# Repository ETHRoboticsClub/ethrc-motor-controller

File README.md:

<h1 align="center">ETHRC Motor Controller</h1>

<p align="center" width="100%">
  
</p>

***

<p align="center">
  
&nbsp; &nbsp; &nbsp; &nbsp;
  
</p>

***

## SPECIFICATIONS

| Parameter | ETHRC Motor Controller v1.0| 
| --- | --- |
| Voltage Input | 33 - 58.8V |
| Peak Electrical Power | TBD |
| Mass | TBD |
| Peak Phase Current | TBD |
| Communication | EtherCat, 5Mbps CAN-FD and SWD interface |
| Cooling | TBD|
| Positioning | 1x Onboard 14-bit Encoder and one external encoder |
| Control rate | TBD |
| PWM Switching Rate | TBD |
| MCU | STM32G474 |
| Dimensions | 88.0 × 88.0 mm |

***

## DIRECTORY STRUCTURE

    .
    ├─ Computations       # Misc calculations
    ├─ DXF_SVG            # Vector graphics
    ├─ HTML               # HTML files for generated webpage
    ├─ Images             # Pictures and renders
    │
    ├─ kibot_resources    # External resources for KiBot
    │  ├─ colors          # Color theme for KiCad
    │  ├─ fonts           # Fonts used in the project
    │  ├─ scripts         # External scripts used with KiBot
    │  └─ templates       # Templates for KiBot generated reports
    │
    ├─ kibot_yaml         # KiBot YAML config files
    ├─ KiRI               # KiRI (PCB diff viewer) files
    │
    ├─ lib                # KiCad footprint and symbol libraries
    │  ├─ 3d_models       # Component 3D models
    │  ├─ lib_fp          # Footprint libraries
    │  └─ lib_sym         # Symbol libraries
    │
    ├─ Logos              # Logos
    │
    ├─ Manufacturing      # Assembly and fabrication documents
    │  ├─ Assembly        # Assembly documents (BoM, pos, notes)
    │  │
    │  └─ Fabrication     # Fabrication documents (ZIP, notes)
    │     ├─ Drill Tables # CSV drill tables
    │     └─ Gerbers      # Gerbers
    │
    ├─ Report             # Reports for ERC/DRC
    ├─ Schematic          # PDF of schematic
    ├─ Templates          # Title block templates
    ├─ Testing
    │  └─ Testpoints      # Testpoints tables      
    │
    └─ Variants           # Outputs for assembly variants

***

## FIRMWARE

***

## CREDITS

Schematic is largely inspired by the moteus controllers designed by Josh Pieper and amulet motion controller designed by Vincent Nguyen. They were modified to meet our own specifications. The CI/CD workflow and the templates for this KiCad 9.0 project was forked from https://github.com/nguyen-v/KDT_Hierarchical_KiBot created by Vincent Nguyen.
***

## PHOTOS

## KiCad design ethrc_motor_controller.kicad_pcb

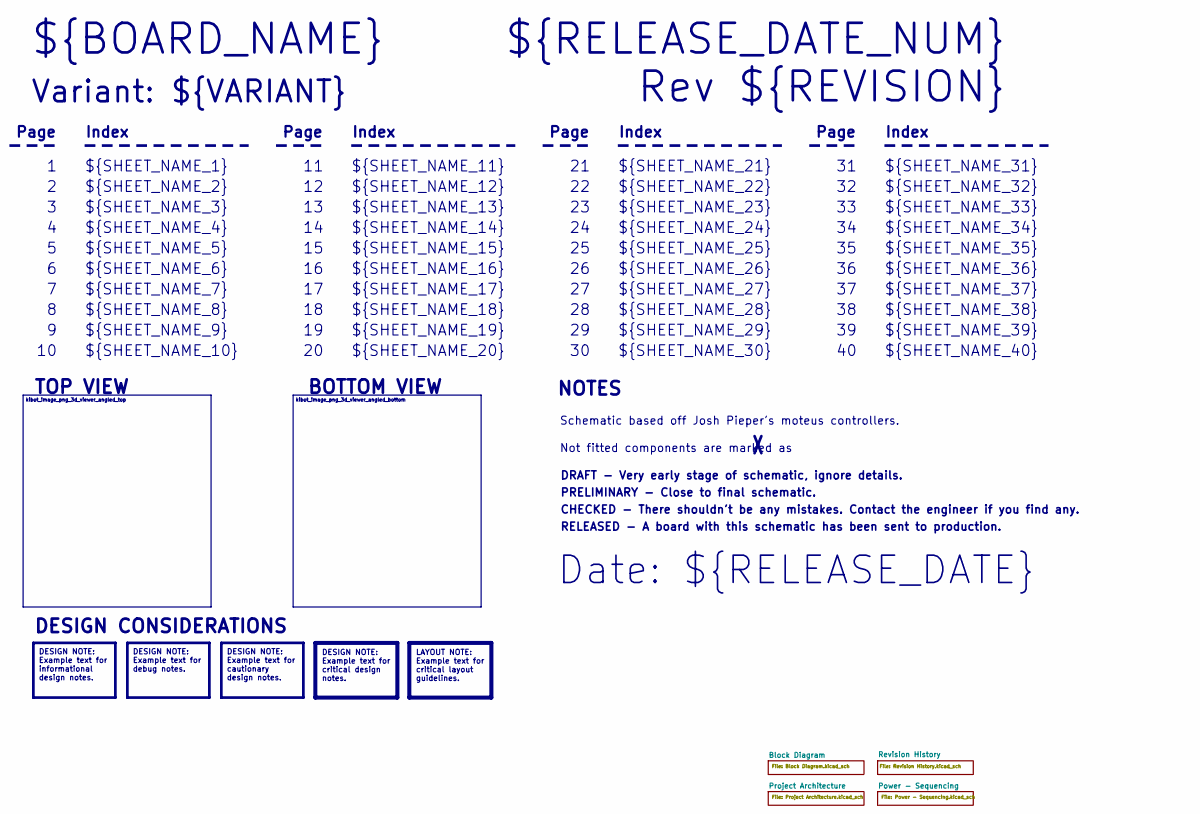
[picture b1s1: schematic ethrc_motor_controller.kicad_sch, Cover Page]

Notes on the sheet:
BOTTOM VIEW
${SHEET_NAME_23}
${SHEET_NAME_10}
RELEASED - A board with this schematic has been sent to production.
${SHEET_NAME_13}
Page
TOP VIEW
${SHEET_NAME_15}
${SHEET_NAME_7}
Not fitted components are marked as
${SHEET_NAME_30}
Index
${SHEET_NAME_18}
PRELIMINARY - Close to final schematic.
Date: ${RELEASE_DATE}
${SHEET_NAME_4}
${SHEET_NAME_27}
${SHEET_NAME_20}
${SHEET_NAME_38}
${SHEET_NAME_9}
${SHEET_NAME_12}
${SHEET_NAME_40}
${SHEET_NAME_19}
${SHEET_NAME_32}
${RELEASE_DATE_NUM}
Variant: ${VARIANT}
${SHEET_NAME_11}
${SHEET_NAME_8}
Rev ${REVISION}
${SHEET_NAME_24}
${SHEET_NAME_29}
${SHEET_NAME_22}
${SHEET_NAME_39}
${SHEET_NAME_5}
${SHEET_NAME_17}
${SHEET_NAME_28}
${SHEET_NAME_31}
${BOARD_NAME}
${SHEET_NAME_26}
${SHEET_NAME_34}

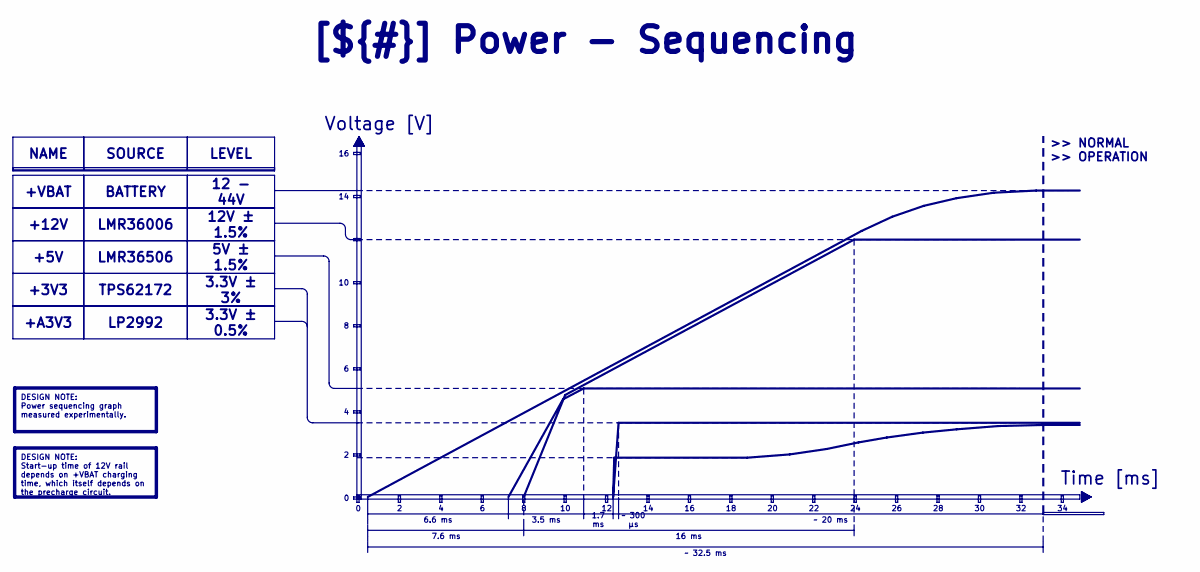
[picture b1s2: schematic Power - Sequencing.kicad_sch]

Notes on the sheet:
Voltage [V]
>> NORMAL >> OPERATION
Time [ms]
3.5 ms
7.6 ms
3.3V ± 0.5%
~ 300 μs
1.7 ms
16 ms
+12V
LP2992
LMR36006
LEVEL
NAME
DESIGN NOTE: Power sequencing graph measured experimentally.
+3V3
~ 20 ms
SOURCE
+5V
DESIGN NOTE: Start-up time of 12V rail depends on +VBAT charging time, which itself depends on the precharge circuit.
[${#}] ${TITLE}
TPS62172
LMR36506
BATTERY
5V ± 1.5%
3.3V ± 3%
+A3V3
+VBAT
6.6 ms
~ 32.5 ms
12V ± 1.5%
12 - 44V

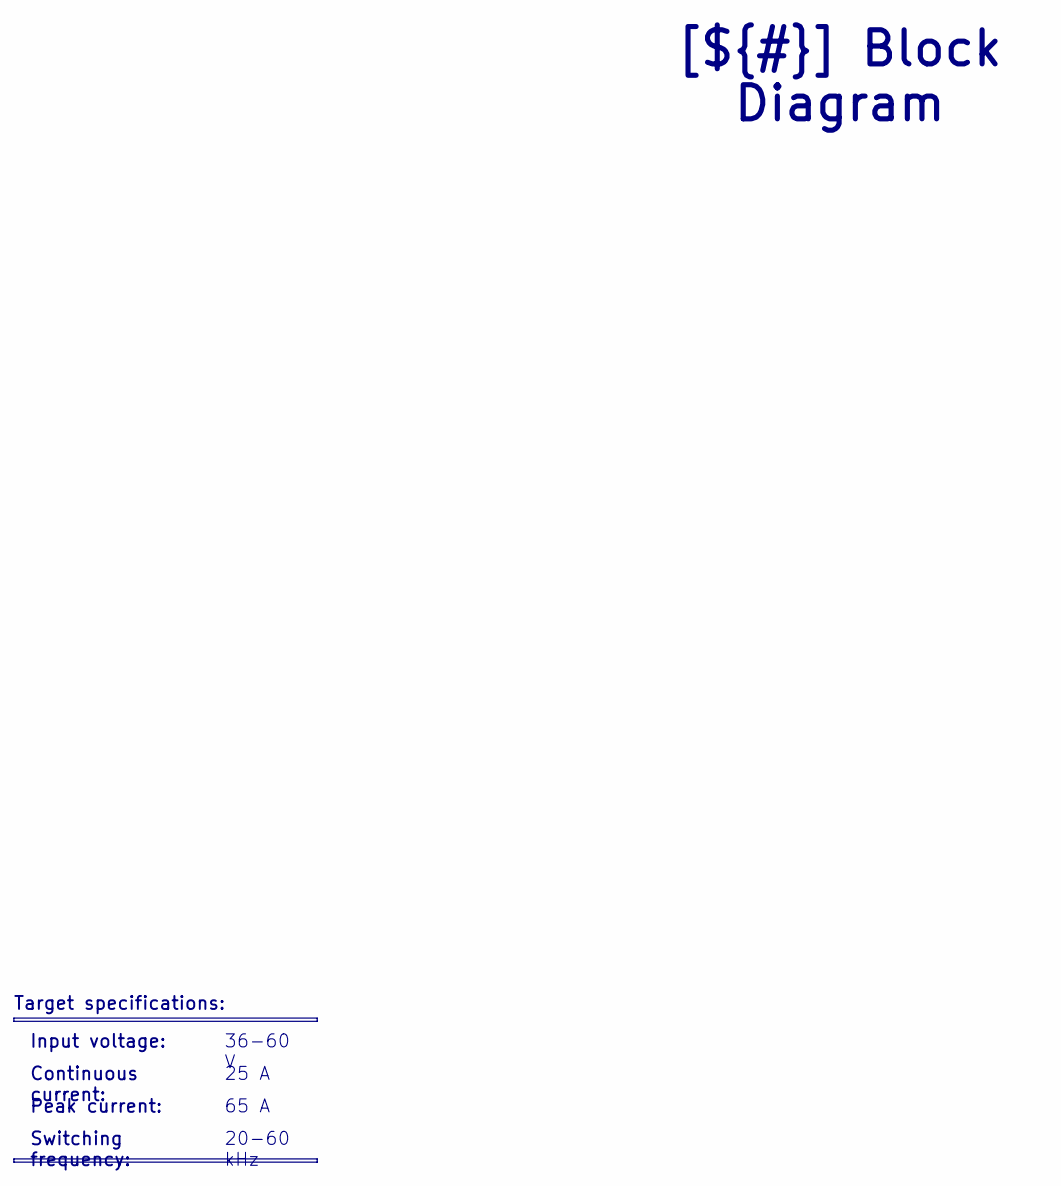
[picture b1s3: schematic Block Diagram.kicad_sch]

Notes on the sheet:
Peak current:
Continuous current:
Input voltage:
20-60 kHz
25 A
[${#}] ${TITLE}
Target specifications:
65 A
36-60 V
Switching frequency:

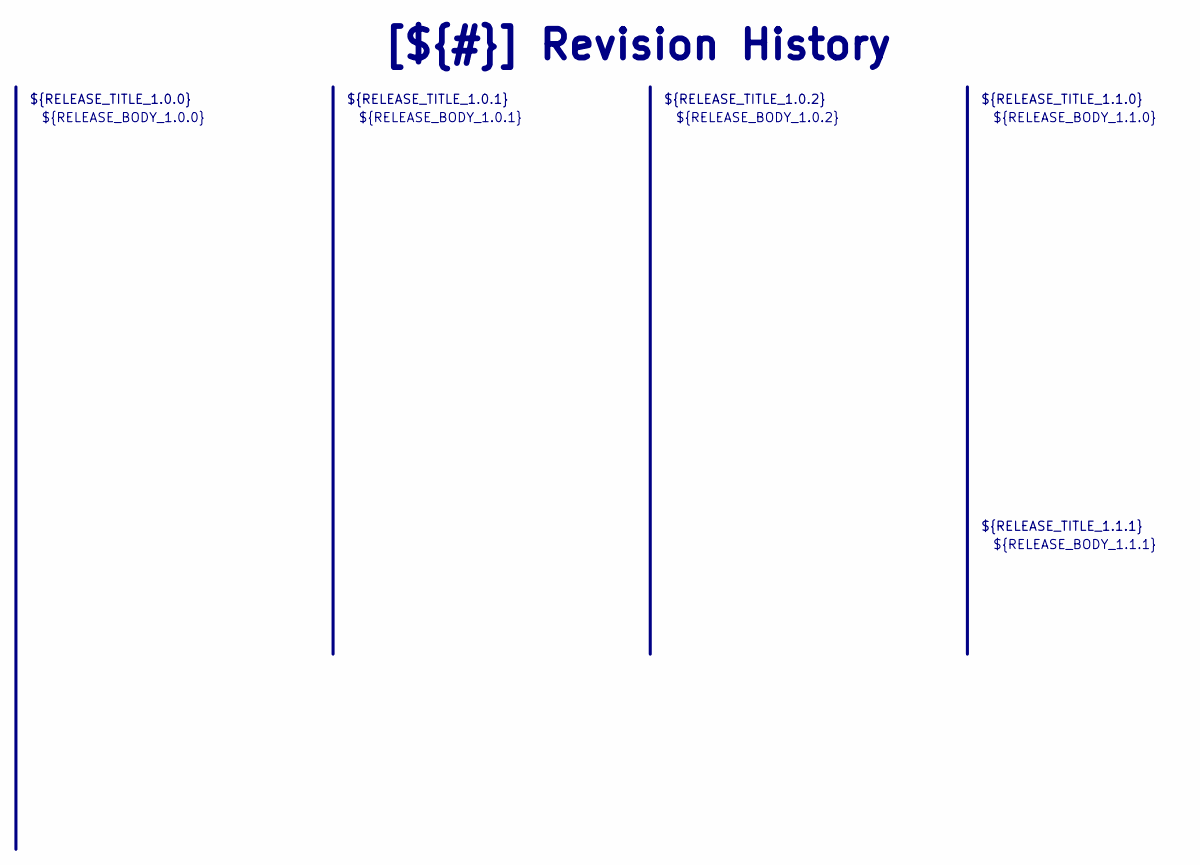
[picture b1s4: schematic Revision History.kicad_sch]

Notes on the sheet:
${RELEASE_BODY_1.1.0}
[${#}] ${TITLE}
${RELEASE_BODY_1.0.0}
${RELEASE_TITLE_1.0.2}
${RELEASE_BODY_1.1.1}
${RELEASE_TITLE_1.1.1}
${RELEASE_BODY_1.0.2}
${RELEASE_BODY_1.0.1}
${RELEASE_TITLE_1.0.0}
${RELEASE_TITLE_1.0.1}
${RELEASE_TITLE_1.1.0}

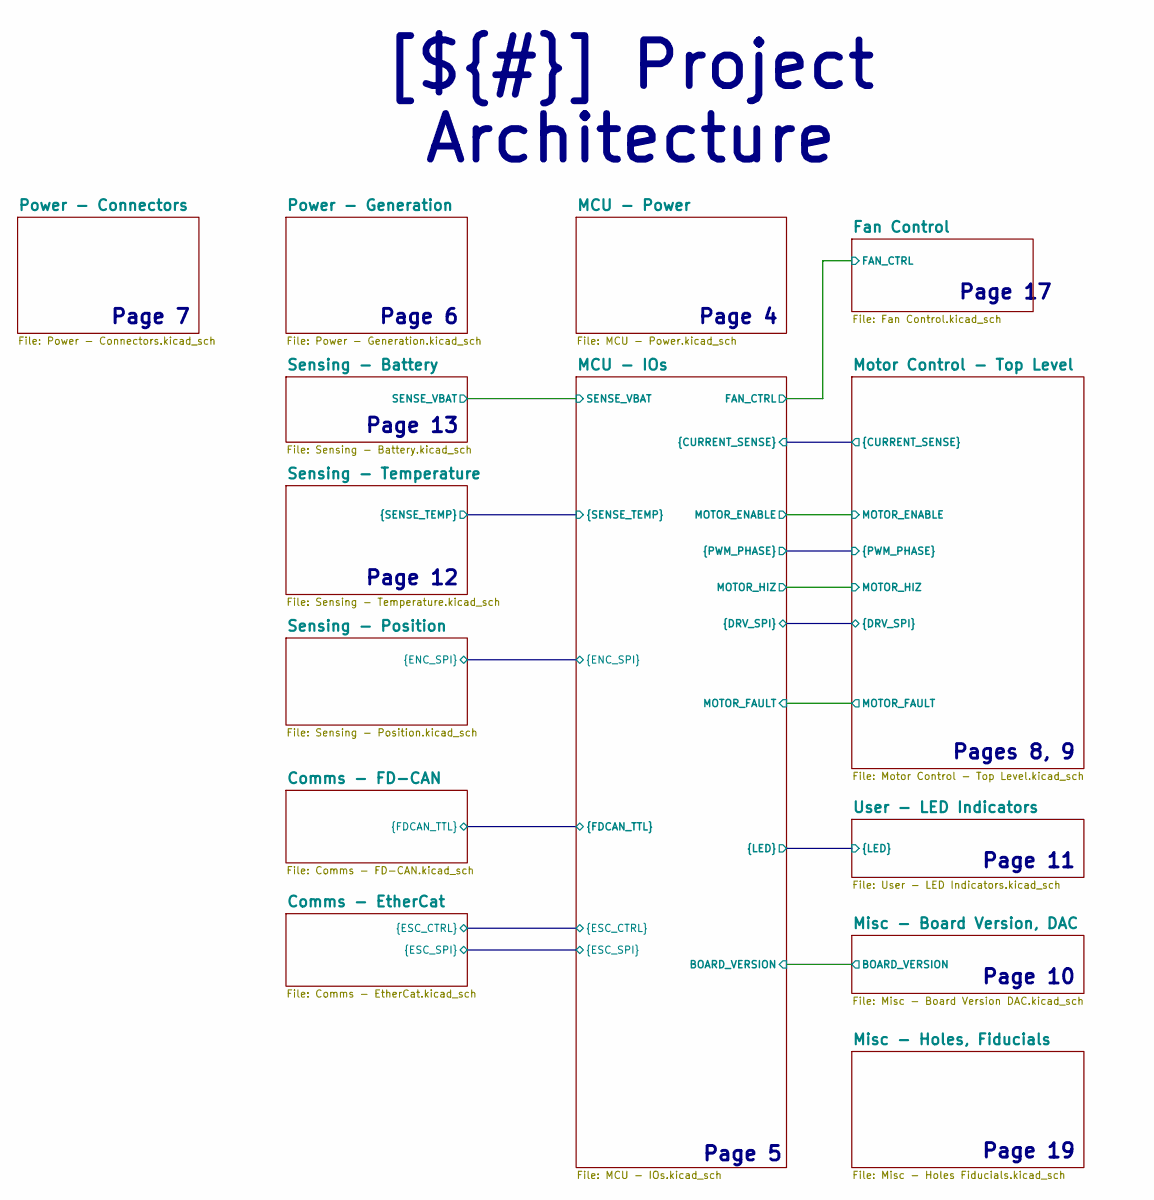
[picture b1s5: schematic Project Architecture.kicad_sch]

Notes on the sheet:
Page 17
Page 13
Page 12
Page 10
Page 7
Pages 8, 9
Page 11
Page 6
Page 4
Page 19
Page 5
[${#}] ${TITLE}

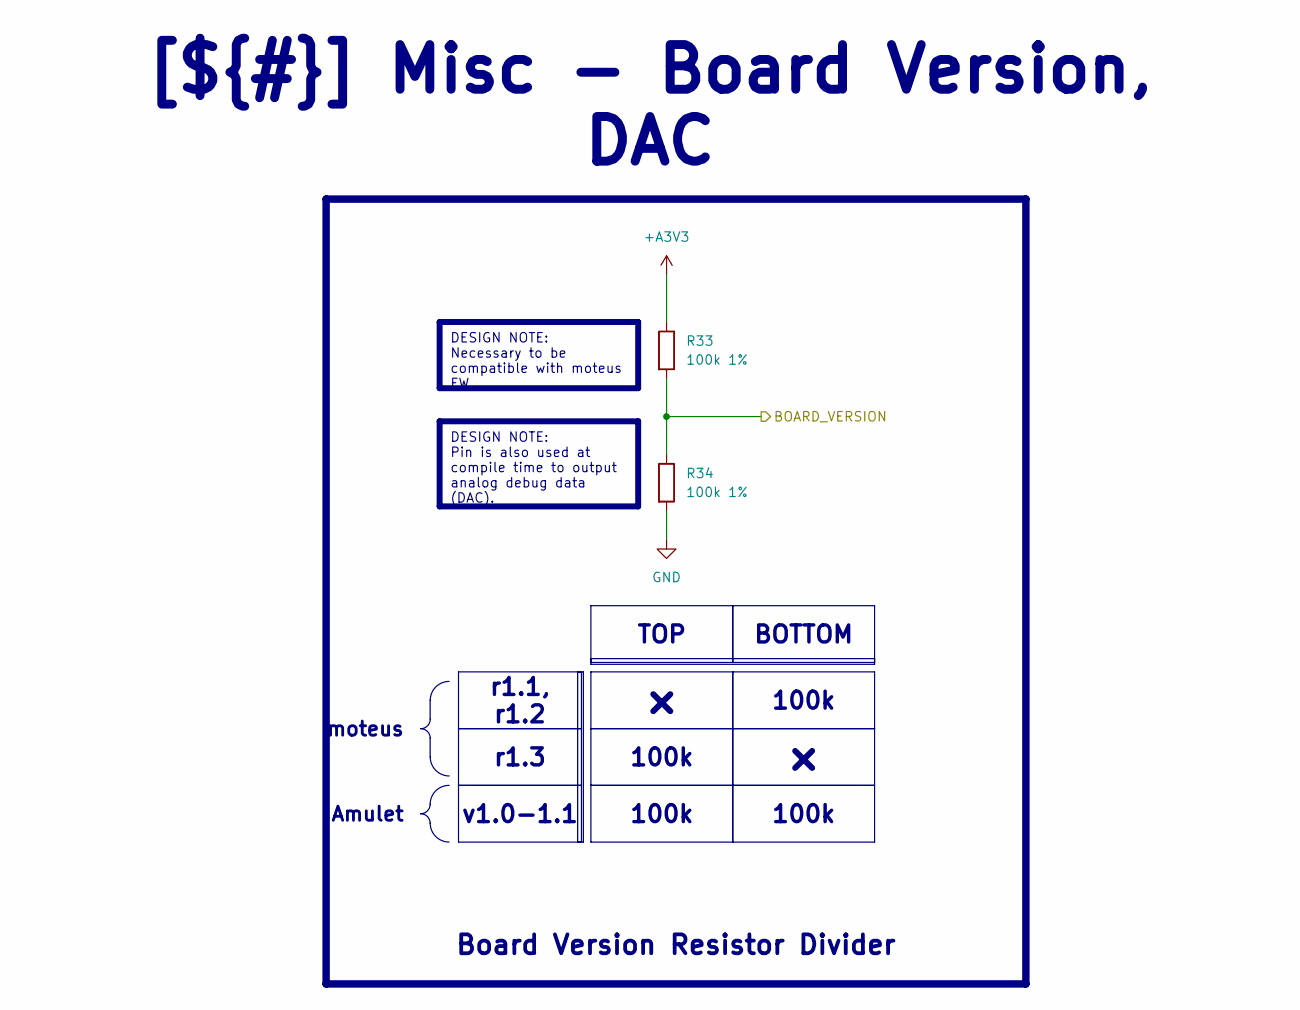
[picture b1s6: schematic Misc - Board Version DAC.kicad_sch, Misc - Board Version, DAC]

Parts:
R33, R34: 100k 1%; R_0402_1005_DensityHigh; Manufacturer Part Number RT0402FRE07100KL

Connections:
+A3V3: R33.1; also elsewhere on the board
/Project Architecture/MCU - IOs/BOARD_VERSION: R33.2, R34.1; also elsewhere on the board
GND: R34.2; also elsewhere on the board

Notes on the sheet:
100k
moteus
r1.3
r1.1, r1.2
DESIGN NOTE: Necessary to be compatible with moteus FW.
Amulet
[${#}] ${TITLE}
DESIGN NOTE: Pin is also used at compile time to output analog debug data (DAC).
Board Version Resistor Divider
BOTTOM
v1.0-1.1
TOP

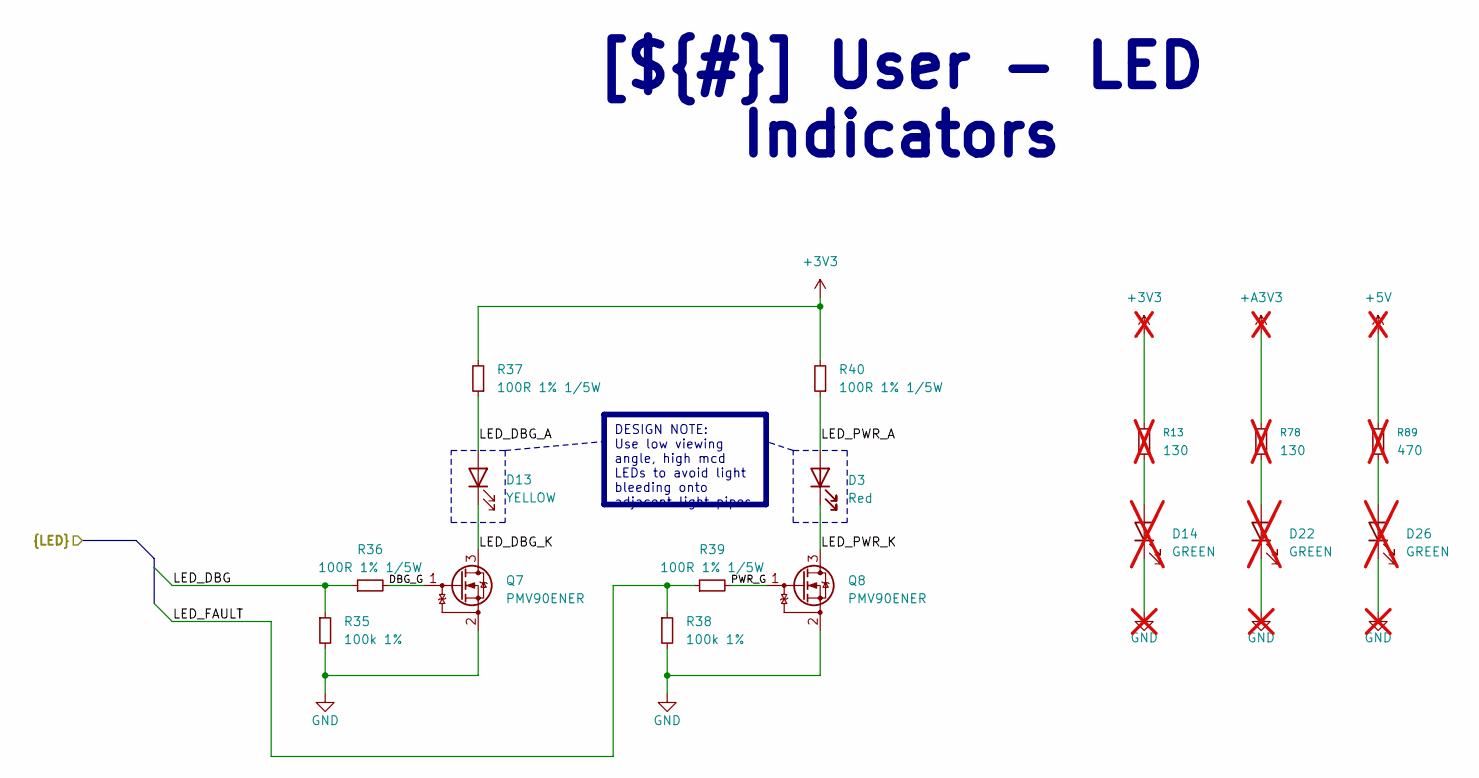
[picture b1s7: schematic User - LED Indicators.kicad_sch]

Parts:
D3: Red; LED_SM1206; Manufacturer Part Number SM1206NHC-IL
D13: YELLOW; LED_SM1206; Manufacturer Part Number SM1206NYC-IL
D14, D22, D26: GREEN; LED_SM1206; Manufacturer Part Number SM1206NPGC-IL; not fitted
Q7, Q8: PMV90ENER; SOT-23-3; Manufacturer Part Number PMV90ENER
R13, R78: 130; R_0402_1005_DensityHigh; not fitted
R35, R38: 100k 1%; R_0402_1005_DensityHigh; Manufacturer Part Number RT0402FRE07100KL
R36, R37, R39, R40: 100R 1% 1/5W; R_0402_1005_DensityHigh; Manufacturer Part Number RCS0402100RFKED
R89: 470; R_0402_1005_DensityHigh; not fitted

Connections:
+3V3: R13.1, R37.2, R40.2; also elsewhere on the board
/Project Architecture/MCU - IOs/LED_DBG: R35.1, R36.1; also elsewhere on the board
/Project Architecture/MCU - IOs/LED_FAULT: R38.1, R39.1; also elsewhere on the board
/Project Architecture/User - LED Indicators/DBG_G: Q7.1 (G), R36.2
/Project Architecture/User - LED Indicators/LED_DBG_A: D13.2 (A), R37.1
/Project Architecture/User - LED Indicators/LED_DBG_K: D13.1 (K), Q7.3 (D)
/Project Architecture/User - LED Indicators/LED_PWR_A: D3.2 (A), R40.1
/Project Architecture/User - LED Indicators/LED_PWR_K: D3.1 (K), Q8.3 (D)
/Project Architecture/User - LED Indicators/PWR_G: Q8.1 (G), R39.2
GND: D14.1 (K), D22.1 (K), D26.1 (K), Q7.2 (S), Q8.2 (S), R35.2, R38.2; also elsewhere on the board
unnamed: D14.2 (A), R13.2
unnamed: D22.2 (A), R78.2
unnamed: D26.2 (A), R89.2

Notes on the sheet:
[${#}] ${TITLE}
DESIGN NOTE: Use low viewing angle, high mcd LEDs to avoid light bleeding onto adjacent light pipes.

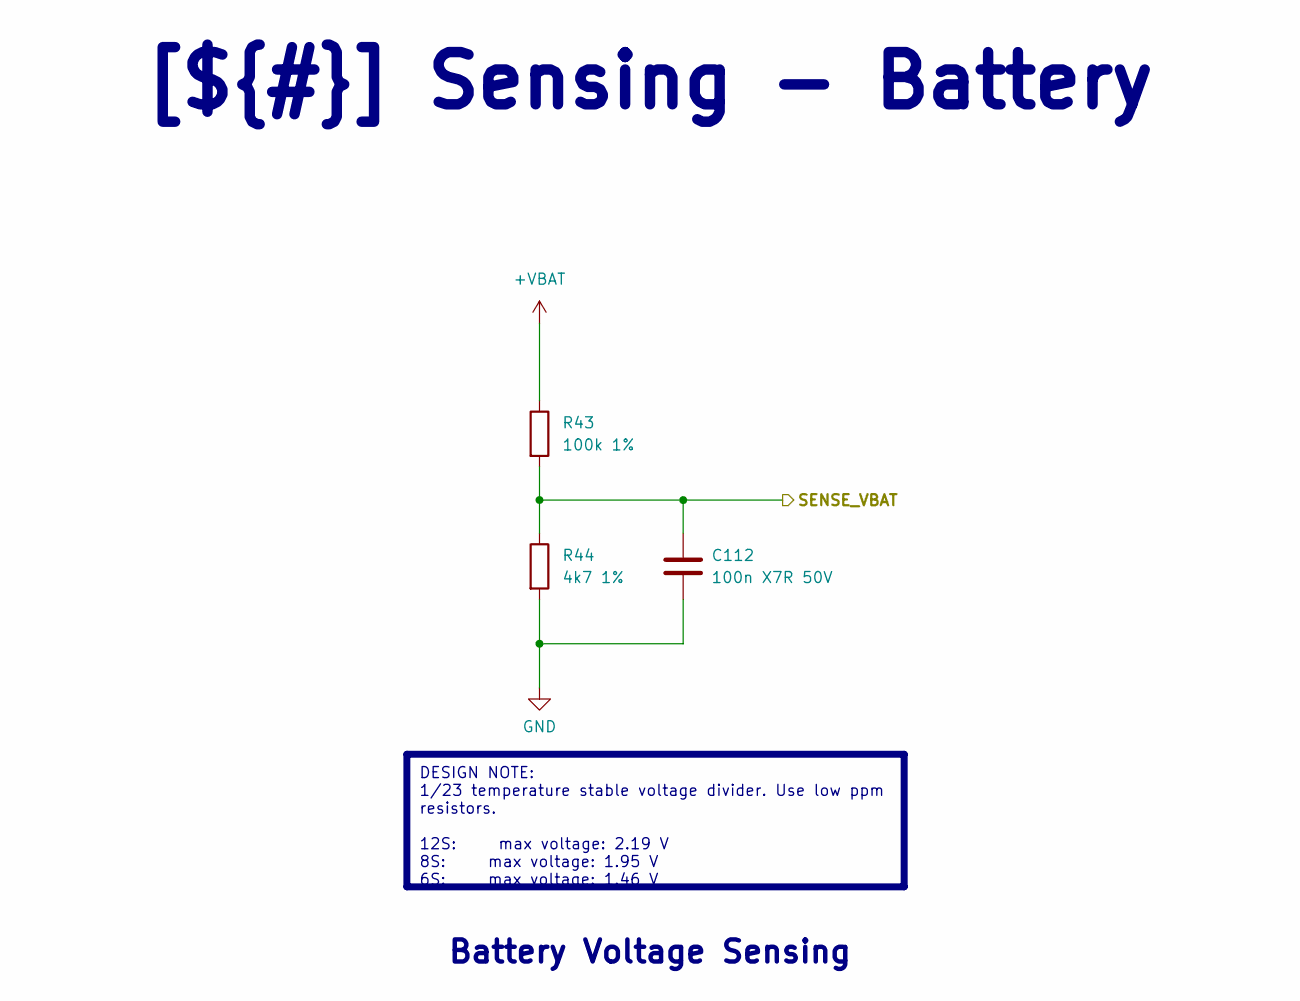
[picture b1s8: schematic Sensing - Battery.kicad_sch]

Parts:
C112: 100n X7R 50V; C_0402_1005_DensityHigh; Manufacturer Part Number GCM155R71H104KE02J
R43: 100k 1%; R_0805_2012_DensityHigh; Manufacturer Part Number ERJ-6ENF1003V
R44: 4k7 1%; R_0402_1005_DensityHigh; Manufacturer Part Number RT0402FRE134K7L

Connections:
+VBAT: R43.1; also elsewhere on the board
/Project Architecture/MCU - IOs/SENSE_VBAT: C112.1, R43.2, R44.1; also elsewhere on the board
GND: C112.2, R44.2; also elsewhere on the board

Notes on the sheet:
[${#}] ${TITLE}
DESIGN NOTE: 1/23 temperature stable voltage divider. Use low ppm resistors. 12S: max voltage: 2.19 V 8S: max voltage: 1.95 V 6S: max voltage: 1.46 V
Battery Voltage Sensing

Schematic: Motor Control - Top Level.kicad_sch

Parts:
C91, C96: 1u X7R 25V; C_0603_1608_DensityHigh; Manufacturer Part Number TMK107AB7105KAHT
C92: 4u7 X7R 100V; C_1206_3216_DensityHighest; Manufacturer Part Number GRJ31CZ72A475KE01L
C93: 100n X7R 16V; C_0402_1005_DensityHigh; Manufacturer Part Number GCM155R71C104KA55D
C94: 47n X7R 100V; C_0603_1608_DensityHigh; Manufacturer Part Number C0603C473K1RECAUTO
C95: 100n X7R 100V; C_0603_1608_DensityHigh; Manufacturer Part Number HMK107B7104KAHT
C97: 1u X7R 6.3V; C_0402_1005_DensityHigh; Manufacturer Part Number GRT155R70J105KE01D
R16, R17: 2k 1%; R_0402_1005_DensityHigh; Manufacturer Part Number ERJ-2RKF2001X
TP59: GHA; TestPoint_Pad_D0.4mm
TP60: GLA; TestPoint_Pad_D0.4mm
TP61: SHA; TestPoint_Pad_D0.4mm
TP62: GHB; TestPoint_Pad_D0.4mm
TP63: GLB; TestPoint_Pad_D0.4mm
TP64: SHB; TestPoint_Pad_D0.4mm
TP65: GHC; TestPoint_Pad_D0.4mm
TP66: GLC; TestPoint_Pad_D0.4mm
TP67: SHC; TestPoint_Pad_D0.4mm
TP68: SA_P; TestPoint_Pad_D0.5mm
TP69: SA_N; TestPoint_Pad_D0.5mm
TP70: SB_P; TestPoint_Pad_D0.5mm
TP71: SB_N; TestPoint_Pad_D0.5mm
TP72: SC_P; TestPoint_Pad_D0.5mm
TP73: SC_N; TestPoint_Pad_D0.5mm
U6: DRV8353FS; WQFN-40-1EP_6x6mm_P0.5mm_EP4.15x4.15mm_ThermalVias; Manufacturer Part Number DRV8353FSRTAR

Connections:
+3V3: R16.1, R17.1; also elsewhere on the board
+A3V3: C93.1, U6.24 (VREF); also elsewhere on the board
+VBAT: C91.1, C92.1, C95.1, U6.3 (VM), U6.4 (VDRAIN); also elsewhere on the board
/Project Architecture/MCU - IOs/DRV_CS: U6.30 (nSCS); also elsewhere on the board
/Project Architecture/MCU - IOs/DRV_MISO: R17.2, U6.27 (SDO); also elsewhere on the board
/Project Architecture/MCU - IOs/DRV_MOSI: U6.28 (SDI); also elsewhere on the board
/Project Architecture/MCU - IOs/DRV_SCLK: U6.29 (SCLK); also elsewhere on the board
/Project Architecture/MCU - IOs/MOTOR_ENABLE: U6.31 (ENABLE); also elsewhere on the board
/Project Architecture/MCU - IOs/MOTOR_FAULT: R16.2, U6.26 (nFAULT); also elsewhere on the board
/Project Architecture/MCU - IOs/MOTOR_HIZ: U6.33 (INLA), U6.35 (INLB), U6.37 (INLC); also elsewhere on the board
/Project Architecture/MCU - IOs/PWM_PHASEA: U6.32 (INHA); also elsewhere on the board
/Project Architecture/MCU - IOs/PWM_PHASEB: U6.34 (INHB); also elsewhere on the board
/Project Architecture/MCU - IOs/PWM_PHASEC: U6.36 (INHC); also elsewhere on the board
/Project Architecture/MCU - IOs/SOA: U6.23 (SOA); also elsewhere on the board
/Project Architecture/MCU - IOs/SOB: U6.22 (SOB); also elsewhere on the board
/Project Architecture/MCU - IOs/SOC: U6.21 (SOC); also elsewhere on the board
/Project Architecture/Motor Control - Top Level/CPH: C94.1, U6.2 (CPH)
/Project Architecture/Motor Control - Top Level/CPL: C94.2, U6.1 (CPL)
/Project Architecture/Motor Control - Top Level/DVDD: C97.1, U6.38 (DVDD)
/Project Architecture/Motor Control - Top Level/GHA: TP59.1, U6.6 (GHA); also elsewhere on the board
/Project Architecture/Motor Control - Top Level/GHB: TP62.1, U6.15 (GHB); also elsewhere on the board
/Project Architecture/Motor Control - Top Level/GHC: TP65.1, U6.16 (GHC); also elsewhere on the board
/Project Architecture/Motor Control - Top Level/GLA: TP60.1, U6.8 (GLA); also elsewhere on the board
/Project Architecture/Motor Control - Top Level/GLB: TP63.1, U6.13 (GLB); also elsewhere on the board
/Project Architecture/Motor Control - Top Level/GLC: TP66.1, U6.18 (GLC); also elsewhere on the board
/Project Architecture/Motor Control - Top Level/SA+: TP68.1, U6.9 (SPA); also elsewhere on the board
/Project Architecture/Motor Control - Top Level/SA-: TP69.1, U6.10 (SNA); also elsewhere on the board
/Project Architecture/Motor Control - Top Level/SB+: TP70.1, U6.12 (SPB); also elsewhere on the board
/Project Architecture/Motor Control - Top Level/SB-: TP71.1, U6.11 (SNB); also elsewhere on the board
/Project Architecture/Motor Control - Top Level/SC+: TP72.1, U6.19 (SPC); also elsewhere on the board
/Project Architecture/Motor Control - Top Level/SC-: TP73.1, U6.20 (SNC); also elsewhere on the board
/Project Architecture/Motor Control - Top Level/SHA: TP61.1, U6.7 (SHA); also elsewhere on the board
/Project Architecture/Motor Control - Top Level/SHB: TP64.1, U6.14 (SHB); also elsewhere on the board
/Project Architecture/Motor Control - Top Level/SHC: TP67.1, U6.17 (SHC); also elsewhere on the board
/Project Architecture/Motor Control - Top Level/VCP: C91.2, U6.5 (VCP)
/Project Architecture/Motor Control - Top Level/VGLS: C96.1, U6.40 (VGLS)
GND: C92.2, C93.2, C95.2, C96.2, C97.2, U6.25 (AGND), U6.39 (GND), U6.41 (EP); also elsewhere on the board

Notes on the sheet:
Page 9
DESIGN NOTE: 3x PWM mode.
[${#}] ${TITLE}
LAYOUT NOTE: Gate drive traces should be short and wide. Ensure good return paths for GH (return in SH) and GL (return in GND).
Test Points
LAYOUT NOTE: Route sense traces as a differential pair. Route away from digital signals.
DESIGN NOTE: Single supply mode: VDRAIN = VM
Gate Drive
LAYOUT NOTE: Route current sense traces away from digital signals. Ensure good return paths.
Three-Phase Inverter
100-V Three-Phase Smart Gate Driver
Kelvin Sense

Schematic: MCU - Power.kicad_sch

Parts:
C1: 4u7 X7R 16V; C_0603_1608_DensityHigh; Manufacturer Part Number GRM188Z71C475KE21J
C2, C6, C9: 1u X7R 10V; C_0402_1005_DensityHigh; Manufacturer Part Number GRM155Z71A105KE01J
C3, C4, C5, C8, C10, C11: 100n X7R 50V; C_0402_1005_DensityHigh; Manufacturer Part Number GCM155R71H104KE02J
C7: 4u7 X5R 25V; C_0402_1005_DensityHigh; Manufacturer Part Number CM05X5R475M25AH
FB1: 1k @ 100MHz; R_0805_2012_DensityHigh; Manufacturer Part Number 742792096
U1: STM32G474RET3; LQFP-64_10x10mm_P0.5mm; Manufacturer Part Number STM32G474RET3

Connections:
+3V3: C1.1, C3.1, C4.1, C5.1, C8.1, C9.1, U1.1 (VBAT), U1.16 (VDD), U1.32 (VDD), U1.48 (VDD), U1.64 (VDD); also elsewhere on the board
+A3V3: C2.1, FB1.1; also elsewhere on the board
/Project Architecture/MCU - Power/F_A3V3: C6.1, C7.1, C10.1, C11.1, FB1.2, U1.28 (VREF+), U1.29 (VDDA)
GND: C1.2, C2.2, C3.2, C4.2, C5.2, C6.2, C7.2, C8.2, C9.2, C10.2, C11.2, U1.15 (VSS), U1.27 (VSSA), U1.31 (VSS), U1.47 (VSS), U1.63 (VSS); also elsewhere on the board

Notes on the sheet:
J. Pieper ADC investigation
STM32G474 Datasheet p.81
AN5346
LAYOUT NOTE: Place each capacitor close to the relevant pin. Minimize loop inductance.
[${#}] ${TITLE}
Microcontroller Power Supply Scheme
DESIGN NOTE: Increased capacitance from 1 uF to 4.7 uF

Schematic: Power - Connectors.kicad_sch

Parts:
D2: SMBJ60A; DIOM5436X244N; Mouser Part Number 576-SMBJ60A
J2: XT60PW-F; AMASS_XT60PW-F_1x02_P7.20mm_Horizontal; Manufacturer Part Number XT60PW-F
J3: XT60PW-M; AMASS_XT60PW-M_1x02_P7.20mm_Horizontal; Manufacturer Part Number XT60PW-M

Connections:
+VBAT: D2.1 (A1), J2.2, J3.2; also elsewhere on the board
CHASSIS: D2.2 (A2), J2.MP2, J3.MP2; also elsewhere on the board
GND: J2.1, J3.1; also elsewhere on the board

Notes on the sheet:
DESIGN NOTE: Do not exceed absolute maximum ratings! Maximum input voltage is 48V
DESIGN NOTE: Do not hot-plug when powered!
LAYOUT NOTE: Place TVS diodes near input power connectors.
[${#}] ${TITLE}
DESIGN NOTE: It's best to power the controller through the male connector to always have a female connector at the end of the chain.
LAYOUT NOTE: Keep sufficient clearance between power nets according to IPC-2221/IEC60664-1

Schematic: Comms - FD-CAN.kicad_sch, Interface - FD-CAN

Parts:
C146, C147: 100n X7R 50V; C_0402_1005_DensityHigh; Manufacturer Part Number GCM155R71H104KE02J
C148: 4n7 X7R 100V; C_0402_1005_DensityHigh; Manufacturer Part Number GCM155R72A472KA37D
D20, D21: PESD2CANFD24V-UX; SOT-323_SC-70; Manufacturer Part Number PESD2CANFD24V-UX
J1, J12: Conn_01x03_Mounting; JST_GH_SM03B-GHS-TB_1x03-1MP_P1.25mm_Horizontal; Manufacturer Part Number SM03B-GHS-TB(LF)(SN)
J11: PTH 01x03 2.54mm; PTH_1x03_P2.54mm
R69: 10k 1%; R_0402_1005_DensityHigh; Manufacturer Part Number RT0402FRE0710KL
R70, R71: 60R4 1% 1/4W; R_0603_1608_DensityHigh; Manufacturer Part Number ESR03EZPF60R4
SW1: CAS-220TA; CAS-220A_NDC-L; Manufacturer Part Number CAS-220TA
U10: TCAN1051HGVDRBRQ1; HVSON-8-1EP_3x3mm_P0.65mm_EP1.6x2.4mm_ThermalVias; Manufacturer Part Number TCAN1051HGVDRBRQ1

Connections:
+3V3: C146.1, U10.5 (VIO); also elsewhere on the board
+5V: C147.1, U10.3 (VCC); also elsewhere on the board
/Project Architecture/Comms - FD-CAN/CAN_TERM_B: R71.2, SW1.4 (A)
/Project Architecture/Comms - FD-CAN/CAN_TERM_MID: C148.1, R70.2, R71.1
/Project Architecture/Comms - FD-CAN/CAN_TERM_T: R70.1, SW1.1 (A)
/Project Architecture/Comms - FD-CAN/FDCAN+: D20.1 (K1), D21.2 (K2), J1.3, J11.3, J12.3, SW1.2 (B), U10.7 (CANH)
/Project Architecture/Comms - FD-CAN/FDCAN-: D20.2 (K2), D21.1 (K1), J1.2, J11.2, J12.2, SW1.5 (B), U10.6 (CANL)
/Project Architecture/Comms - FD-CAN/FDCAN_RX: U10.4 (RXD); also elsewhere on the board
/Project Architecture/Comms - FD-CAN/FDCAN_S: R69.1, U10.8 (S)
/Project Architecture/Comms - FD-CAN/FDCAN_TX: U10.1 (TXD); also elsewhere on the board
CHASSIS: D20.3 (CC), D21.3 (CC), J1.MP1, J1.MP2, J12.MP1, J12.MP2; also elsewhere on the board
GND: C146.2, C147.2, C148.2, J1.1, J11.1, J12.1, R69.2, U10.2 (GND), U10.9 (PAD); also elsewhere on the board

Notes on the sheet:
LAYOUT NOTE: Place close to FD-CAN connector if possible to reduce stub length.
DESIGN NOTE: Only connect GND if connected device does not share ground!
LAYOUT NOTE: FD-CAN should be routed as a 120-ohm differential pair.
[${#}] ${TITLE}
DESIGN NOTE: Silent mode disabled.
DESIGN NOTE: PTH pads can be used for directly soldering wires if top part is broken off.
DESIGN NOTE: Split termination helps with filtering common-mode noise.

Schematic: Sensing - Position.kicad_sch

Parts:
C113: 1u; C_0402_1005_DensityHigh; Manufacturer Part Number GRM155Z71A105KE01J
D17: PESD4USB5B-TBSX; SOT1176D; Manufacturer Part Number PESD4USB5B-TBSX
J8: Conn_01x06_Shield_Mounting; JST_GH_SM06B-GHS-TB_1x06-1MP_P1.25mm_Horizontal; Manufacturer Part Number SM06B-GHS-TB(LF)(SN)
R10, R45: 22R; R_0402_1005_DensityHigh; Manufacturer Part Number ERJ-2RKF22R0X
U7: MA732GQ-Z; QFN-16_MA732; Manufacturer Part Number MA732GQ-Z

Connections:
+3V3: C113.1, J8.1, U7.13 (VDD); also elsewhere on the board
/Project Architecture/MCU - IOs/ENC_BRD_CS: U7.5 (CS); also elsewhere on the board
/Project Architecture/MCU - IOs/ENC_EXT_CS: D17.1 (K), D17.10 (K), J8.6; also elsewhere on the board
/Project Architecture/MCU - IOs/ENC_MISO: D17.4 (K), D17.7 (K), R10.1, R45.1; also elsewhere on the board
/Project Architecture/MCU - IOs/ENC_MOSI: D17.2 (K), D17.9 (K), J8.5, U7.4 (MOSI); also elsewhere on the board
/Project Architecture/MCU - IOs/ENC_SCLK: D17.5 (K), D17.6 (K), J8.3, U7.12 (SCLK); also elsewhere on the board
/Project Architecture/Sensing - Position/ENC_MISO_IC: R45.2, U7.7 (MISO)
CHASSIS: D17.3 (A), D17.8 (A), J8.MP1, J8.MP2; also elsewhere on the board
GND: C113.2, J8.2, U7.8 (GND), U7.10 (TEST), U7.17 (PAD); also elsewhere on the board
unnamed: J8.4, R10.2

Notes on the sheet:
External 14-Bit On-Axis Magnetic Rotary Position Sensor (disambiguation)
[${#}] ${TITLE}
LAYOUT NOTE: Place commutation encoder at the center of the board. Right now it is quite close to current-carrying traces but the chip should be immune to stray magnetic fields.
14-Bit On-Axis Magnetic Rotary Position Sensor (commutation)

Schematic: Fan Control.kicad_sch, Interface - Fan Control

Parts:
C149: 4u7 X7R 16V; C_0603_1608_DensityHigh; Manufacturer Part Number GRM188Z71C475KE21J; not fitted
C150, C151: 100n X7R 50V; C_0402_1005_DensityHigh; Manufacturer Part Number GCM155R71H104KE02J; not fitted
J14: S2B-PH-SM4-TB; JST_PH_S2B-PH-SM4-TB_1x02-1MP_P2.00mm_Horizontal; Manufacturer Part Number S2B-PH-SM4-TB; not fitted
Q9: PMV90ENER; SOT-23-3; Manufacturer Part Number PMV90ENER; not fitted
R72: 10R 1%; R_0603_1608_DensityHigh; Manufacturer Part Number CRCW060310R0FKEAHP; not fitted
TP74: FAN_SW; TestPoint_Pad_D0.5mm; not fitted
U11: DGD0216WT-7; TSOT-23-5; Manufacturer Part Number DGD0216WT-7; not fitted

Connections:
unnamed: C149.1, C150.1, U11.5 (VCC)
unnamed: C149.2, C150.2, C151.2, Q9.2 (S), U11.2 (COM)
unnamed: C151.1, J14.1
unnamed: J14.2, Q9.3 (D), TP74.1
unnamed: J14.MP1, J14.MP2
unnamed: Q9.1 (G), R72.2
unnamed: R72.1, U11.4 (OUT)

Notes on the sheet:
Low-side Fan Switch and Gate Driver
DESIGN NOTE: Gate driver is not strictly necessary for hysteresis control but could be useful for PWM control.
DESIGN NOTE: Gate resistor should be chosen to reduce slew rate of FET.
[${#}] ${TITLE}

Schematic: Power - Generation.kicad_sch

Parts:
C18, C20: 2u2; C_0805_2012_DensityHigh; Manufacturer Part Number CGA4J1X7R2A225K125AC; not fitted
C21, C23: 4u7; C_1206_3216_DensityHigh; Manufacturer Part Number GRJ31CZ72A475KE01L; not fitted
C24, C26, C163: 1u; C_1210_3225_DensityHigh; Manufacturer Part Number MSASH32NSB7105KTNA01
C25, C27: 220n; C_0603_1608_DensityHigh; Manufacturer Part Number HMK107C7224KAHTE; not fitted
C28: 1u; C_0402_1005_DensityHigh; Manufacturer Part Number GRM155Z71A105KE01J; not fitted
C29: 100n; C_0805_2012_DensityHigh; Manufacturer Part Number C2012X7R2A104K125AA
C30: 100n; C_0402_1005_DensityHigh; Manufacturer Part Number GCM155R71H104KE02J; not fitted
C31: 100n; C_0402_1005_DensityHigh; Manufacturer Part Number GRM155R71C104KA88D
C32, C40: 15u; C_1210_3225_DensityHigh; Manufacturer Part Number CGA6M3X7R1E156M200AB; not fitted
C33, C34, C35, C36, C37, C38, C41, C42, C43, C44, C45, C46, C48, C49, C50, C52, C53, C54, C55, C56, C57, C59, C60, C61, C63, C64, C65, C66, C67, C68, C70, C71, C72, C73, C74, C75, C76, C77, C78, C80, C81, C82, C83, C84, C85, C88, C89, C90: 4u7; C_1206_3216_DensityHigh; Manufacturer Part Number GRJ31CZ72A475KE01L
C39, C162: 47u; C_1206_3216_DensityHigh; Manufacturer Part Number GRM31CR61A476KE15L
C51: 10u; C_0805_2012_DensityHigh; Manufacturer Part Number C0805C106K8PACTU
C58: 100n; C_0805_2012_DensityHigh; Manufacturer Part Number 08053C104KAT2A
C62: 1u; C_0603_1608_DensityHigh; Manufacturer Part Number TMK107AB7105KAHT
C69: 10n; C_0402_1005_DensityHigh; Manufacturer Part Number GRM155R71C103KA01D
C79: 10n; C_0402_1005_DensityHigh; Manufacturer Part Number HMR105B7103KV-F
C86: 4u7; C_0603_1608_DensityHigh; Manufacturer Part Number GRM188Z71C475KE21J
C87: 22u; C_0603_1608_DensityHigh; Manufacturer Part Number GRM188R60J226MEA0D
FB3: 1k; R_0805_2012_DensityHigh; Manufacturer Part Number 742792096; not fitted
L1: 22u; INDPM108102X400N; Manufacturer Part Number IHLP4040DZER220M11
L2: 22u; L_Coilcraft_LPS4018; Manufacturer Part Number LPS4018-223MRC; not fitted
NT2: FB_12V; NetTie-2_SMD_Pad0.2mm; not fitted
R11: 100k; R_0402_1005_DensityHigh; Manufacturer Part Number RT0402FRE07100KL; not fitted
R12: 9.09k; R_0402_1005_DensityHigh; Manufacturer Part Number RT0402FRE079K09L; not fitted
R14: 15.8k; R_0402_1005_DensityHigh; Manufacturer Part Number CRCW040215K8FKED
R15, R82: 10k; R_0402_1005_DensityHigh; Manufacturer Part Number CRCW040210K0FKED
R79: 64.9k; R_0603_1608_DensityHigh; Manufacturer Part Number CRCW060364K9FKEA
R80: 100k; R_0603_1608_DensityHigh; Manufacturer Part Number CRCW0603100KFKEA
R81: 40.2k; R_0402_1005_DensityHigh; Manufacturer Part Number CRCW040240K2FKED
TP39, TP40, TP41: +VBAT; TestPoint_Pad_D0.5mm
TP46, TP47: +5V; TestPoint_Pad_D0.5mm
TP48, TP49, TP50: +3V3; TestPoint_Pad_D0.5mm
TP51: +A3V3; TestPoint_Pad_D0.5mm
TP52, TP53, TP54, TP55, TP56, TP57, TP58: GND; TestPoint_Pad_D0.5mm
U2: LMR38020SDDAR; LMR38020; Manufacturer Part Number LMR38020SDDAR
U3: LMR36006FSCQ; LMR36006; Manufacturer Part Number LMR36006FSCQRNXRQ1; not fitted
U4: LP2992IM5-3.3/NOPB; SOT-23-5; Manufacturer Part Number LP2992IM5-3.3/NOPB
U5: TPSM861253RDXR; VREG_TPSM861253RDXR; PARTREV B

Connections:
+3V3: C87.1, TP48.1, TP49.1, TP50.1, U5.3 (VOUT), U5.7 (VOS); also elsewhere on the board
+5V: C39.1, C51.1, C58.1, C62.1, C162.1, L1.2, R14.1, R80.2, R81.1, TP46.1, TP47.1, U4.1 (VIN), U4.3 (ON/~OFF), U5.1 (VIN); also elsewhere on the board
+A3V3: C86.1, TP51.1, U4.5 (VOUT); also elsewhere on the board
+VBAT: C18.1, C24.1, C26.1, C29.1, C33.1, C34.1, C35.1, C36.1, C37.1, C38.1, C41.1, C42.1, C43.1, C44.1, C45.1, C46.1, C48.1, C49.1, C50.1, C52.1, C53.1, C54.1, C55.1, C56.1, C57.1, C59.1, C60.1, C61.1, C63.1, C64.1, C65.1, C66.1, C67.1, C68.1, C70.1, C71.1, C72.1, C73.1, C74.1, C75.1, C76.1, C77.1, C78.1, C80.1, C81.1, C82.1, C83.1, C84.1, C85.1, C88.1, C89.1, C90.1, C163.1, FB3.1, TP39.1, TP40.1, TP41.1, U2.2 (EN), U2.3 (VIN); also elsewhere on the board
/Project Architecture/Power - Generation/ADJ_A3V3: C79.1, U4.4 (ADJ)
/Project Architecture/Power - Generation/SW_5V: C31.2, L1.1, U2.8 (SW)
GND: C18.2, C20.2, C21.2, C23.2, C24.2, C25.2, C26.2, C27.2, C28.2, C29.2, C32.2, C33.2, C34.2, C35.2, C36.2, C37.2, C38.2, C39.2, C40.2, C41.2, C42.2, C43.2, C44.2, C45.2, C46.2, C48.2, C49.2, C50.2, C51.2, C52.2, C53.2, C54.2, C55.2, C56.2, C57.2, C58.2, C59.2, C60.2, C61.2, C62.2, C63.2, C64.2, C65.2, C66.2, C67.2, C68.2, C69.2, C70.2, C71.2, C72.2, C73.2, C74.2, C75.2, C76.2, C77.2, C78.2, C79.2, C80.2, C81.2, C82.2, C83.2, C84.2, C85.2, C86.2, C87.2, C88.2, C89.2, C90.2, C162.2, C163.2, R12.2, R15.2, R79.2, R82.2, TP52.1, TP53.1, TP54.1, TP55.1, TP56.1, TP57.1, TP58.1, U2.1 (GND), U2.9 (EP), U3.1 (PGND), U3.6 (AGND), U3.11 (PGND), U4.2 (GND), U5.4 (PGND); also elsewhere on the board
unnamed: C20.1, C21.1, C23.1, C25.1, C27.1, FB3.2, U3.2 (VIN), U3.9 (EN), U3.10 (VIN)
unnamed: C28.1, U3.5 (VCC)
unnamed: C30.1, L2.1, U3.3 (NC), U3.12 (SW)
unnamed: C30.2, U3.4 (BOOT)
unnamed: C32.1, C40.1, L2.2, NT2.2
unnamed: NT2.1, R11.1
unnamed: R11.2, R12.1, U3.7 (FB)
unnamed: C31.1, U2.7 (BOOT)
unnamed: R81.2, R82.1, U2.5 (FB)
unnamed: R80.1, U2.6 (PG)
unnamed: R79.1, U2.4 (RT/SYNC)
unnamed: C69.1, R14.2, R15.1, U5.6 (EN)

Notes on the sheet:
3.3V ± 1% 1A Buck Regulator (1.4MHz)
3.3V ± 0.5% 250mA Linear Regulator
DESIGN NOTE: X6S 10uF is marginally better (but worse DC bias derating) at a higher price.
Voltage Regulators
LAYOUT NOTE: Route feedback traces away from switching node.
5V ± 1% 2A Buck Regulator (400kHz)
Power Rails
Ground
12V ± 1.5% 600mA Buck Regulator (2.1MHz)
LAYOUT NOTE: Minimize switching node loop areas.
DC-Link Bulk Capacitors. 48 x 4.7 uF = 225.6 uF (??? uF at 48V)
Test Points
DESIGN NOTE: An external precharge circuit is advised to charge the bulk capacitors if multiple boards are connected.
Battery
[${#}] ${TITLE}

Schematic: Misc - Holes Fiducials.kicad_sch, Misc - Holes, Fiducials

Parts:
C114, C152, C153, C154: 1n X7R 1kV; C_0603_1608_DensityHigh; Manufacturer Part Number C0603V102KDRAC7867
FM1, FM2, FM3, FM4, FM5, FM6: Fiducial; Fiducial_1mm_Mask2mm
H1, H2, H3, H4: M3; MountingHole_3.2mm_M3_Pad_Via
R73, R75, R76: 0R; R_0603_1608_DensityHigh; Manufacturer Part Number CRCW06030000Z0EAHP; not fitted
R74: 0R; R_0603_1608_DensityHigh; Manufacturer Part Number CRCW06030000Z0EAHP

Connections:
CHASSIS: C114.1, C152.1, C153.1, C154.1, H1.1, H2.1, H3.1, H4.1, R73.1, R74.1, R75.1, R76.1; also elsewhere on the board
GND: C114.2, C152.2, C153.2, C154.2, R73.2, R74.2, R75.2, R76.2; also elsewhere on the board

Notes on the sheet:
Front
Back
DESIGN NOTE: 0-Ohm resistor provides low-impedance bond between chassis and signal GND. Be aware of ground loops through cable shield.
[${#}] ${TITLE}
Fiducial Markers
Mounting Holes and Chassis Connection
DESIGN NOTE: Optional RC filter for chassis grounding. Capacitors offer multi-point low-impedance connections at high-frequencies.
